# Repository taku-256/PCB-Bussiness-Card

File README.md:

# WS2812B with PIC Microcontroller
created by taku-256 @taku_8bits

PICマイコンでNeoPixcelライブラリなしでWS2812Bの制御をする基板です。
高専ロボコン2023用に作成したものを改良しました。

2024年3月現在、部内ロボコンの回路、制御のワンオペ作業に追われているためDCDCを実装した際の動作確認ができていません。
それを除いた動作は確認しておりますので、ぜひ実際に実装して遊んでいただけると嬉しいです。

使用したマイコンはPIC18F26Q84で10MHzの水晶発振子をつけて動かしています。
この基板はこのマイコンの評価基板としても使えるようにピンヘッダーをつけられるようになっているのでPICマイコンに触れてみたい人は是非使ってみてください。

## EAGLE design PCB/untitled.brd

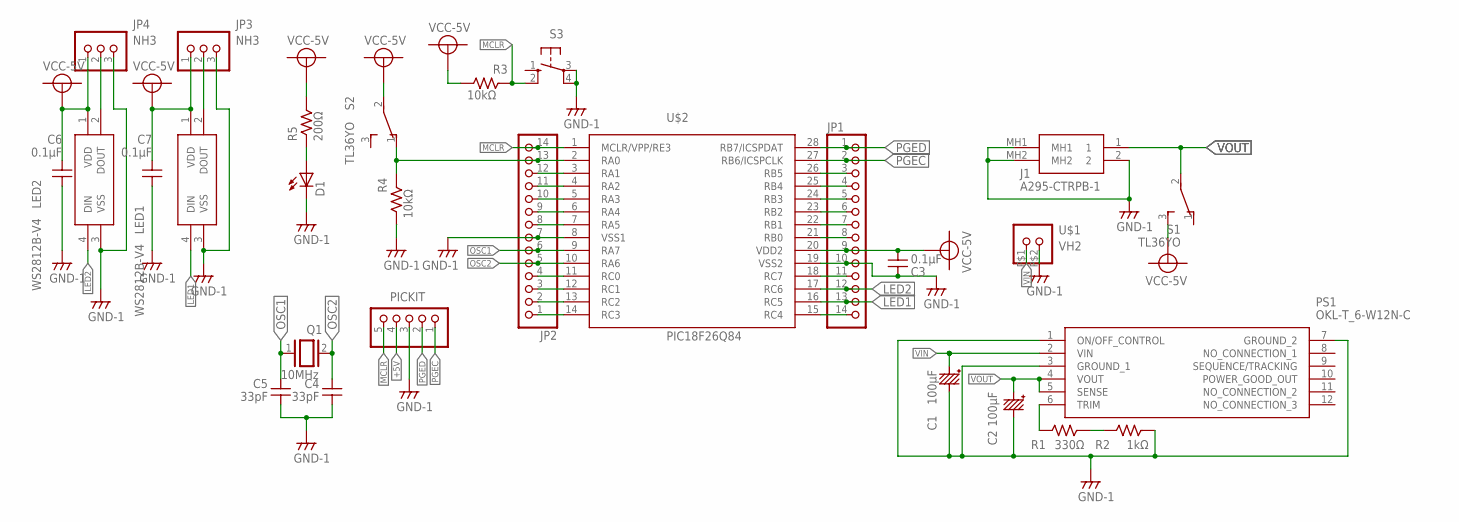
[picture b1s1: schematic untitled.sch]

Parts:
C1, C2: 100μF; CC:3
C3: 0.1μF; C:1
C4, C5: 33pF; C:1
C6, C7: 0.1μF; C1608
D1: LED""""; CHIPLED_0603
J1: A295-CTRPB-1; A295CTRPB1
JP1, JP2: PINHD-1X14; 1X14
JP3, JP4: NH3
LED1, LED2: WS2812B-V4; WS2812BV4
PICKIT: PINHD-1X5/90; 1X05/90
PS1: OKL-T_6-W12N-C; OKLT6W12NC
Q1: 10MHz; QS
R1: 330Ω; C3216
R2: 1kΩ; 2012
R3, R4: 10kΩ; 2012
R5: 200Ω; C3216
S1, S2: TL36YO; TL3XYO
S3: 10-XX; B3F-10XX
U$1: VH2
U$2: PIC18F26Q84; DIL28-3

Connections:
+5V: C3.P$1, C6.2, C7.2, JP1.9, JP3.1, JP4.1, LED1.1 (VDD), LED2.1 (VDD), PICKIT.4, R3.1, R5.2, S1.3 (S), S2.2, U$2.20 (VDD2)
GND: C1.- (P$2-), C2.- (P$2-), C3.P$2, C4.P$1, C5.P$1, C6.1, C7.1, D1.C, J1.2, J1.MH1, J1.MH2, JP1.10, JP2.7, JP3.3, JP4.3, LED1.3 (VSS), LED2.3 (VSS), PICKIT.3, PS1.1 (ON/OFF_CONTROL), PS1.3 (GROUND_1), PS1.7 (GROUND_2), R2.2, R4.1, S3.3, S3.4 (P1), U$1.P$2, U$2.8 (VSS1), U$2.19 (VSS2)
LED1: JP1.13, LED1.4 (DIN), U$2.16 (RC5)
LED2: JP1.12, LED2.4 (DIN), U$2.17 (RC6)
MCLR: JP2.14, PICKIT.5, R3.2, S3.2 (S1), U$2.1 (MCLR/VPP/RE3)
unnamed: JP4.2, LED2.2 (DOUT)
unnamed: JP2.13, R4.2, S2.1 (O), U$2.2 (RA0)
unnamed: JP2.12, U$2.3 (RA1)
unnamed: JP2.11, U$2.4 (RA2)
unnamed: JP2.10, U$2.5 (RA3)
unnamed: JP2.9, U$2.6 (RA4)
unnamed: JP2.8, U$2.7 (RA5)
unnamed: PS1.6 (TRIM), R1.1
unnamed: R1.2, R2.1
unnamed: JP2.4, U$2.11 (RC0)
unnamed: JP2.3, U$2.12 (RC1)
unnamed: JP2.2, U$2.13 (RC2)
unnamed: JP2.1, U$2.14 (RC3)
unnamed: D1.A, R5.1
unnamed: JP1.8, U$2.21 (RB0)
unnamed: JP3.2, LED1.2 (DOUT)
unnamed: JP1.7, U$2.22 (RB1)
unnamed: JP1.6, U$2.23 (RB2)
unnamed: JP1.5, U$2.24 (RB3)
unnamed: JP1.4, U$2.25 (RB4)
unnamed: JP1.3, U$2.26 (RB5)
unnamed: JP1.11, U$2.18 (RC7)
unnamed: JP1.14, U$2.15 (RC4)
OSC1: C5.P$2, JP2.6, Q1.1, U$2.9 (RA7)
OSC2: C4.P$2, JP2.5, Q1.2, U$2.10 (RA6)
PGEC: JP1.2, PICKIT.1, U$2.27 (RB6/ICSPCLK)
PGED: JP1.1, PICKIT.2, U$2.28 (RB7/ICSPDAT)
VIN: C1.+ (P$1+), PS1.2 (VIN), U$1.P$1
VOUT: C2.+ (P$1+), J1.1, PS1.4 (VOUT), PS1.5 (SENSE), S1.2

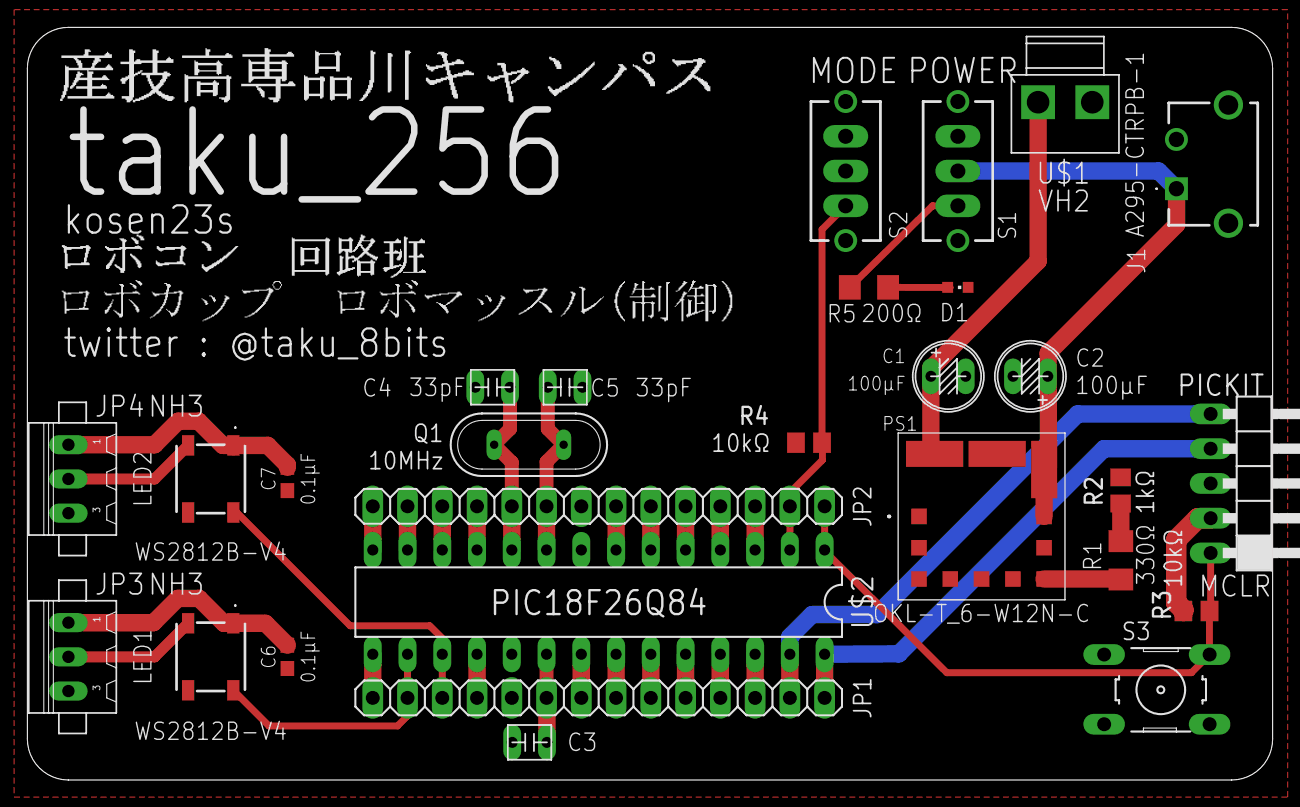
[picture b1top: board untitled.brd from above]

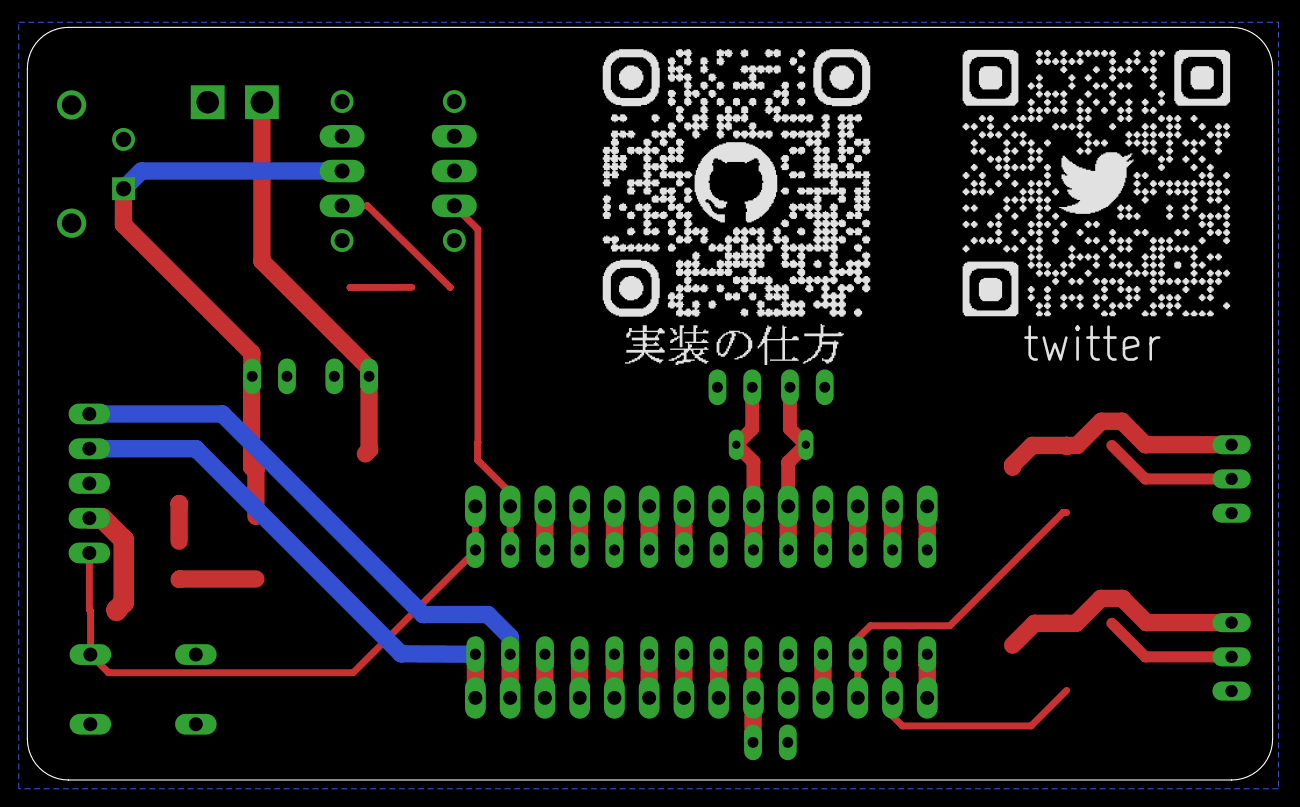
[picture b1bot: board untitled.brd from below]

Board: 2 copper layers, 91.0 x 55.0 mm, 34 parts (3 on the bottom side), 34 nets.

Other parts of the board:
U$10: HOWTOMAKE
U$11: TMCIT
U$13: TWITTER
U$14: MEISHI-GIT-QR
U$15: ROBOCON
U$16: ROBOMUSCLE

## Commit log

2024-01-18 サンプルプログラムのアップロード
2024-01-26 基板の設計データの公開
2024-01-26 回路図等のPDF版でのアップロード
